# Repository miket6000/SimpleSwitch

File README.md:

# SimpleSwitch

SimpleSwitch is a magneticly operated electronic switch designed for model rocketry. It is a 15x10mm PCB with an input and output capable of switching approximately 4A continuous and 10A for 10s. It can accept an input voltage of up to 12V and also includes reverse polarity protection to prevent damage to the switch or downstream electronics in the event that the battery is accidentally connected backwards.

It is designed specifically to be easy to turn on, but to require multiple steps to turn off. This is to prevent issues with accidental turn off which can occur with traditional magnetic switches when they pass by magnatized hardware on launch towers/rails.

The magnetic switch draws a very small amount of power from the battery when plugged in. This is calculated at 3uA worst case, so a small 150mAh 1s battery should last approximately 5 years. On larger batteries this is quickly swamped by the batteries self discharge rate.

## Operation

Use of the SimpleSwitch is easy. Bringing a magnetic south pole near the top of the board will result in the switch turning on and illuminating both the red and green LEDs, the switch is now in the "ON" state. 

To turn off the switch you nead to put a North pole near the switch which will cause the red LED to turn off ("OK" state). Bringing a South pole near the switch will then cause the green LED to turn off and the red LED to turn back on ("WARNING" State). One more north pole will cause the red LED to turn off and the switch to disable the output ("OFF" State).

In summary as you alernate South-\>North-\>South-\>North you step through the states as shown below:

| Magnetic Pole | State Name  | Red LED | Green LED | Switch State |
|---------------|-------------|---------|-----------|--------------|
|               | OFF         | OFF     | OFF       | OFF          |
| SOUTH         | ON          | ON      | ON        | ON           |
| NORTH         | OK          | OFF     | ON        | ON           |
| SOUTH         | WARNING     | ON      | OFF       | ON           |
| NORTH         | OFF         | OFF     | OFF       | OFF          |

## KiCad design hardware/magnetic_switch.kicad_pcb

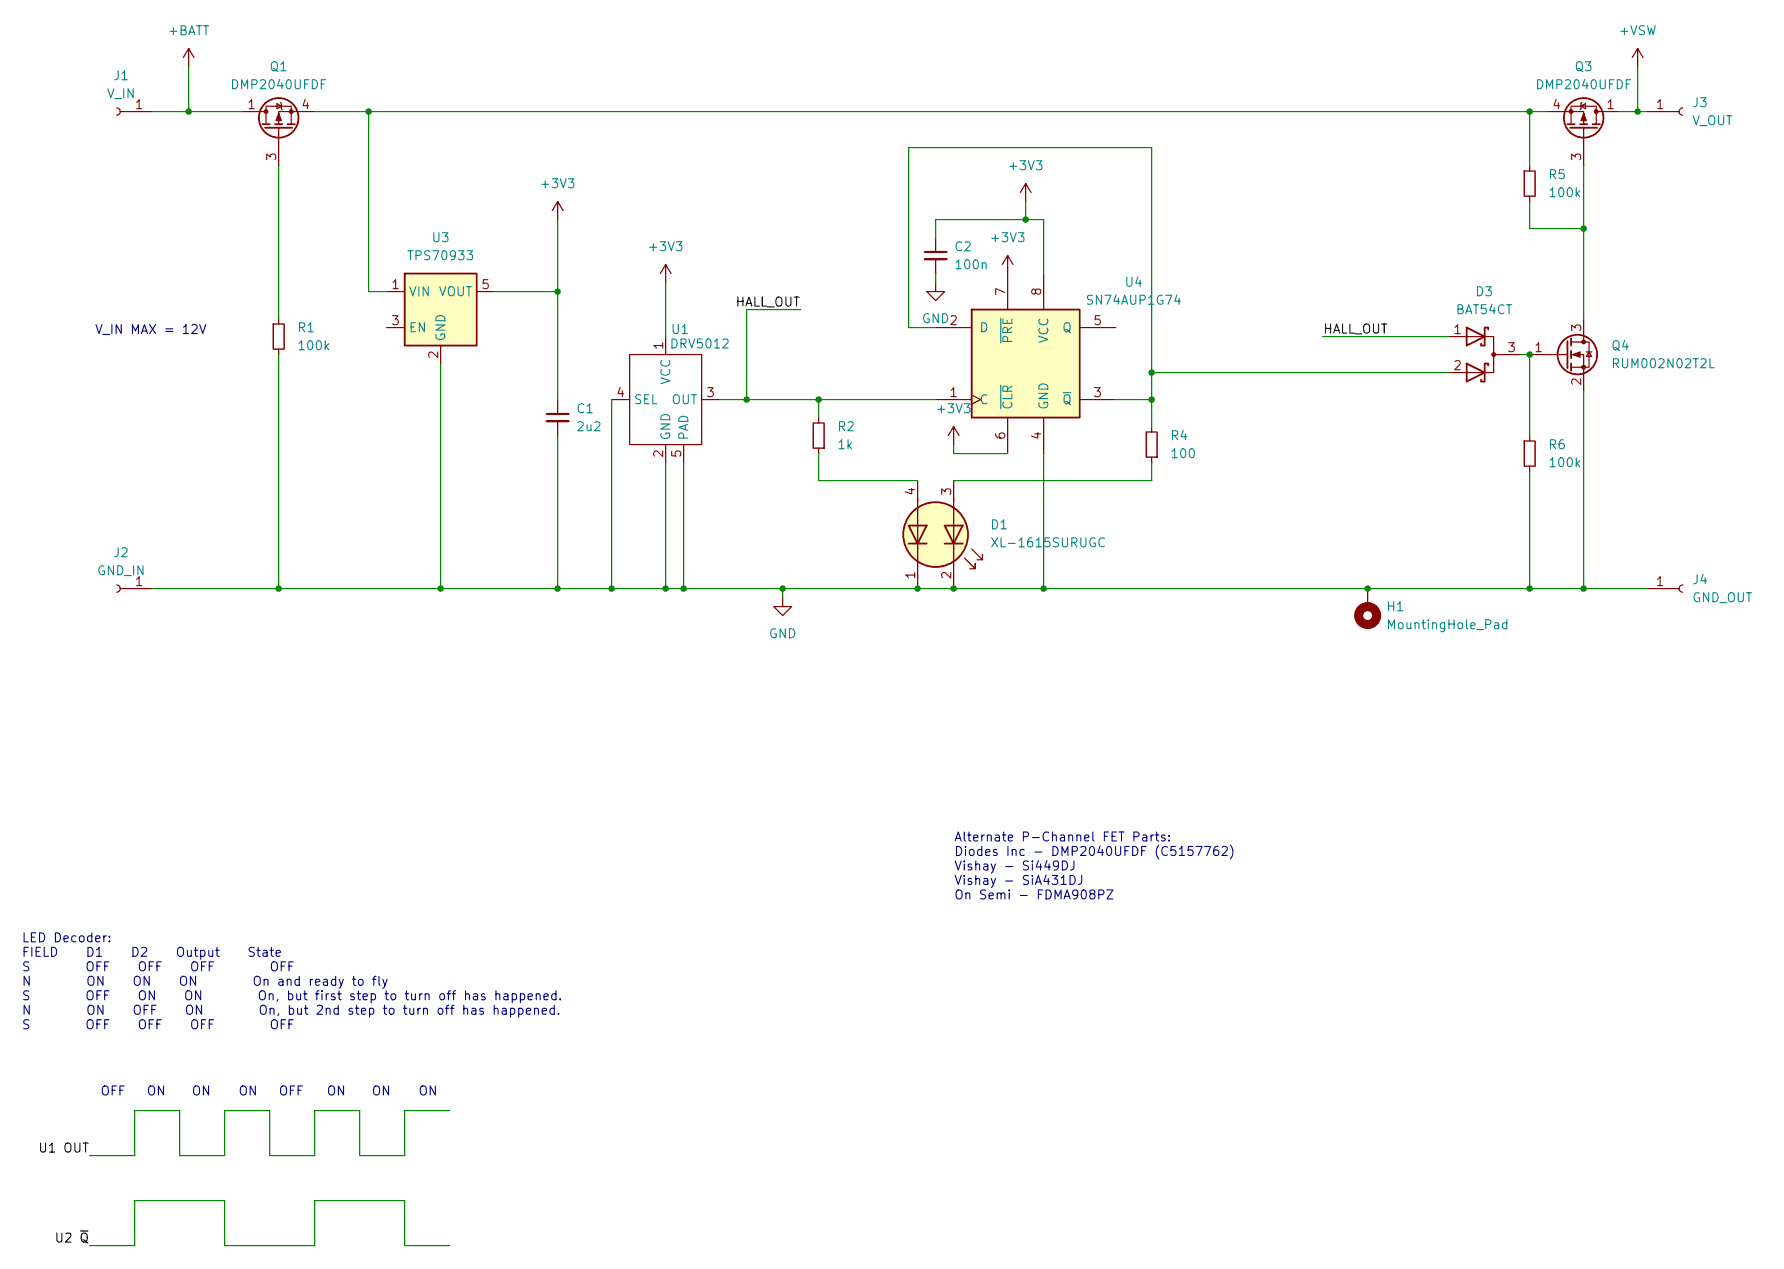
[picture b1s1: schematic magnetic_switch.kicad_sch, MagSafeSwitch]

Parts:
C1: 2u2; C_0402_1005Metric
C2: 100n; C_0402_1005Metric
D1: XL-1615SURUGC; LED_SMT_DUAL_1615; JLCPCB Part # C965839
D3: BAT54CT; SOT-523; JLCPCB Part # C134407
H1: MountingHole_Pad; MountingHole_2.2mm_M2_DIN965_Pad
J1: V_IN; WireSolderPad_w_hole
J2: GND_IN; WireSolderPad_w_hole
J3: V_OUT; WireSolderPad_w_hole
J4: GND_OUT; WireSolderPad_w_hole
Q1, Q3: DMP2040UFDF; Vishay_PowerPAK_SC70-6L_Single; JLCPCB Part # C5157762
Q4: RUM002N02T2L; SOT-723; JLCPCB Part # C250130
R1, R5, R6: 100k; R_0402_1005Metric
R2: 1k; R_0402_1005Metric
R4: 100; R_0402_1005Metric
U1: DRV5012; X2SON_4_EP; JLCPCB Part # C2655038
U3: TPS70933; SOT-23-5; JLCPCB Part # C89347
U4: SN74AUP1G74; X2SON-8_1.4x1mm_P0.35mm; JLCPCB Part # C2677745

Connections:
+3V3: C1.1, C2.1, U1.1 (VCC), U3.5 (VOUT), U4.6 (~CLR), U4.7 (~PRE), U4.8 (VCC)
+BATT: J1.1, Q1.1 (D)
+VSW: J3.1, Q3.1 (D)
/HALL_OUT: D3.1 (A), R2.2, U1.3 (OUT), U4.1 (C)
GND: C1.2, C2.2, D1.1 (K2), D1.2 (K1), H1.1, J2.1, J4.1, Q4.2 (S), R1.2, R6.2, U1.2 (GND), U1.4 (SEL), U1.5 (PAD), U3.2 (GND), U4.4 (GND)
unnamed: D1.3 (A1), R4.1
unnamed: D1.4 (A2), R2.1
unnamed: D3.3 (K), Q4.1 (G), R6.1
unnamed: Q1.3 (G), R1.1
unnamed: Q1.4 (S), Q3.4 (S), R5.1, U3.1 (VIN)
unnamed: Q3.3 (G), Q4.3 (D), R5.2
unnamed: D3.2 (A), R4.2, U4.2 (D), U4.3 (~Q)

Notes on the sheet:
OFF
LED Decoder: FIELD D1 D2 Output State S OFF OFF OFF OFF N ON ON ON On and ready to fly S OFF ON ON On, but first step to turn off has happened. N ON OFF ON On, but 2nd step to turn off has happened. S OFF OFF OFF OFF
V_IN MAX = 12V
Alternate P-Channel FET Parts: Diodes Inc - DMP2040UFDF (C5157762) Vishay - Si449DJ Vishay - SiA431DJ On Semi - FDMA908PZ

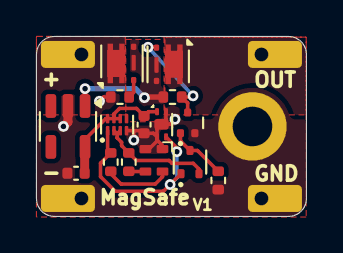
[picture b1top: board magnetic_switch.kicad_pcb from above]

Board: 2 copper layers, 15.0 x 10.0 mm, 20 parts (0 on the bottom side), 12 nets.

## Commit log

2024-12-06 Minor cleanup of the schematic
2025-02-07 Corrected issue with regulator enable pin which needs to be left floating, NOT tied to VCC and updated README to reflect the fact that testing is complete.
2025-02-10 updated pdf schematic to match KiCAD schematic
2025-11-07 updated to smaller components and re-layed out.
2025-11-08 added a linear regulator to allow up to +12V input. This version was sent for manufacture.
2025-11-08 Updated to represent the latest version of the hardware
2025-11-08 Corrected hosted images and added render to readme
2025-11-08 corrected image link url
2025-11-08 Updated state table to include magnetic poles
2025-11-08 Added discussion of input voltage to readme.
2025-11-09 added missing via on R1 gnd
